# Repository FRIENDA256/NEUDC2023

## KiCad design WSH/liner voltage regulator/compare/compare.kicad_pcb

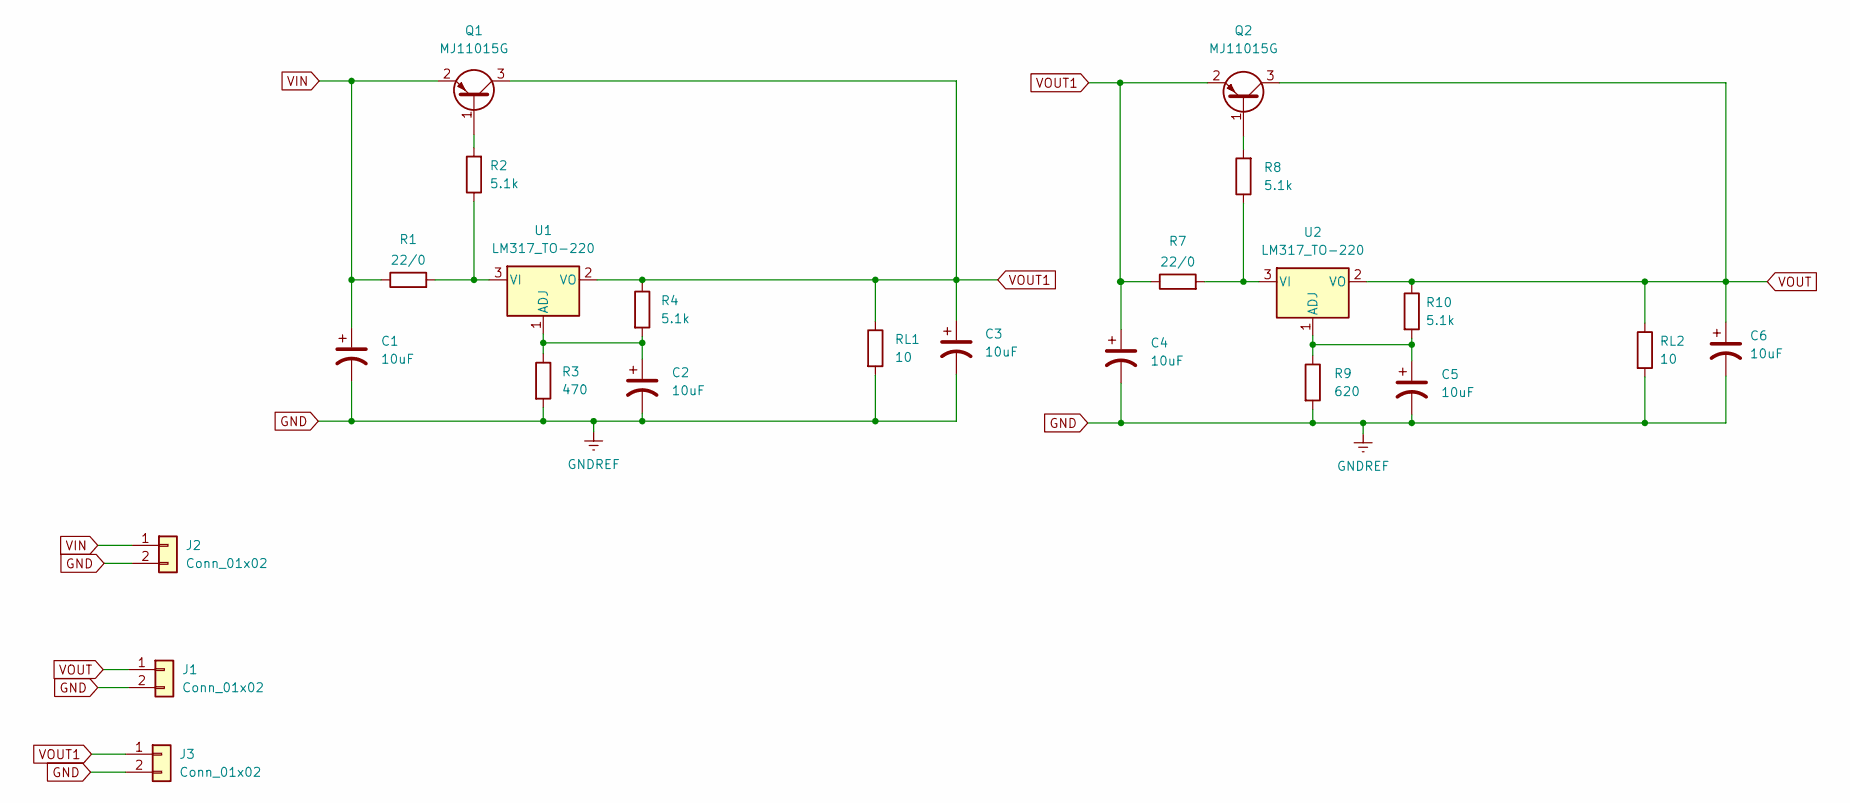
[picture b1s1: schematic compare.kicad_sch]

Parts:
C1, C2, C3, C4, C5, C6: 10uF; CP_EIA-6032-20_AVX-F
J1, J2, J3: Conn_01x02; connector_128-5.08mm3.81
Q1, Q2: MJ11015G; TO-3
R1, R7: 22/0; R_0805_2012Metric
R2, R4, R8, R10: 5.1k; R_0805_2012Metric
R3: 470; R_0805_2012Metric
R9: 620; R_0805_2012Metric
RL1, RL2: 10; R_0805_2012Metric
U1, U2: LM317_TO-220; TO-220-3_Vertical

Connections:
GND: C1.2, C2.2, C3.2, C4.2, C5.2, C6.2, J1.2, J2.2, J3.2, R3.2, R9.2, RL1.2, RL2.2
unnamed: C2.1, R3.1, R4.2, U1.1 (ADJ)
unnamed: C5.1, R9.1, R10.2, U2.1 (ADJ)
unnamed: R1.2, R2.1, U1.3 (VI)
unnamed: Q1.1 (B), R2.2
unnamed: R7.2, R8.1, U2.3 (VI)
unnamed: Q2.1 (B), R8.2
VIN: C1.1, J2.1, Q1.2 (E), R1.1
VOUT: C6.1, J1.1, Q2.3 (C), R10.1, RL2.1, U2.2 (VO)
VOUT1: C3.1, C4.1, J3.1, Q1.3 (C), Q2.2 (E), R4.1, R7.1, RL1.1, U1.2 (VO)

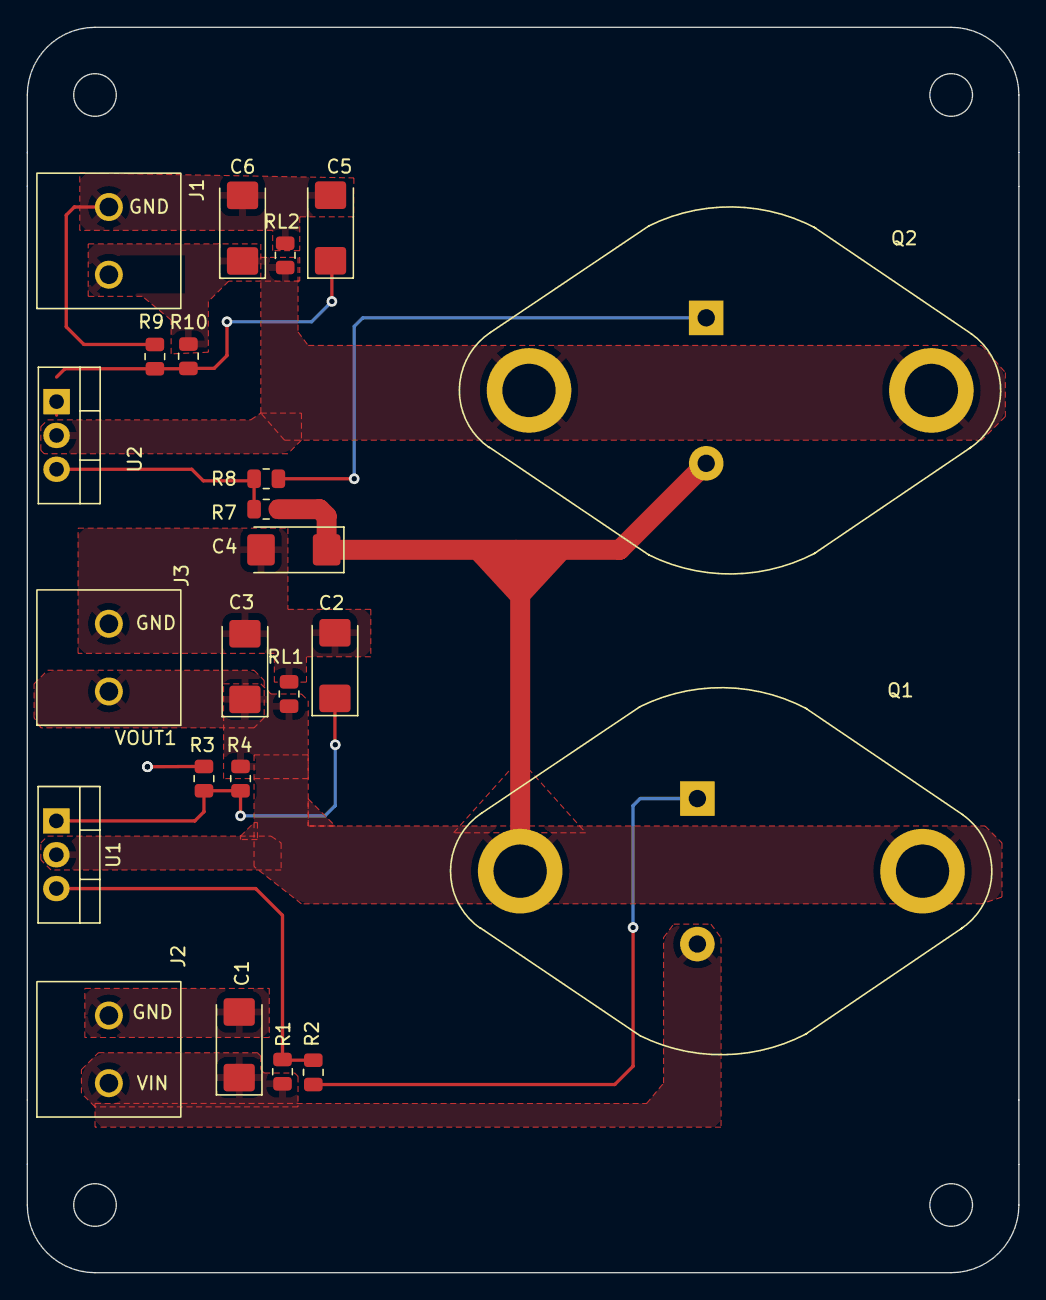
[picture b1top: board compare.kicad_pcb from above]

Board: 2 copper layers, 74.4 x 93.5 mm, 23 parts (0 on the bottom side), 10 nets.

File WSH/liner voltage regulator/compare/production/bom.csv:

Designator,Footprint,Quantity,Value,LCSC Part #
"C1, C2, C3, C4, C5, C6",CP_EIA-6032-20_AVX-F,6,10uF,
"J1, J2, J3",connector_128-5.08mm3.81,3,Conn_01x02,
"Q1, Q2",TO-3,2,MJ11015G,
"R1, R7",0805,2,22/0,
"R10, R2, R4, R8",0805,4,5.1k,
R3,0805,1,470,
R9,0805,1,620,
"RL1, RL2",0805,2,10,
"U1, U2",TO-220-3_Vertical,2,LM317_TO-220,

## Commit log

2023-07-10 test
2023-07-10 Compare
